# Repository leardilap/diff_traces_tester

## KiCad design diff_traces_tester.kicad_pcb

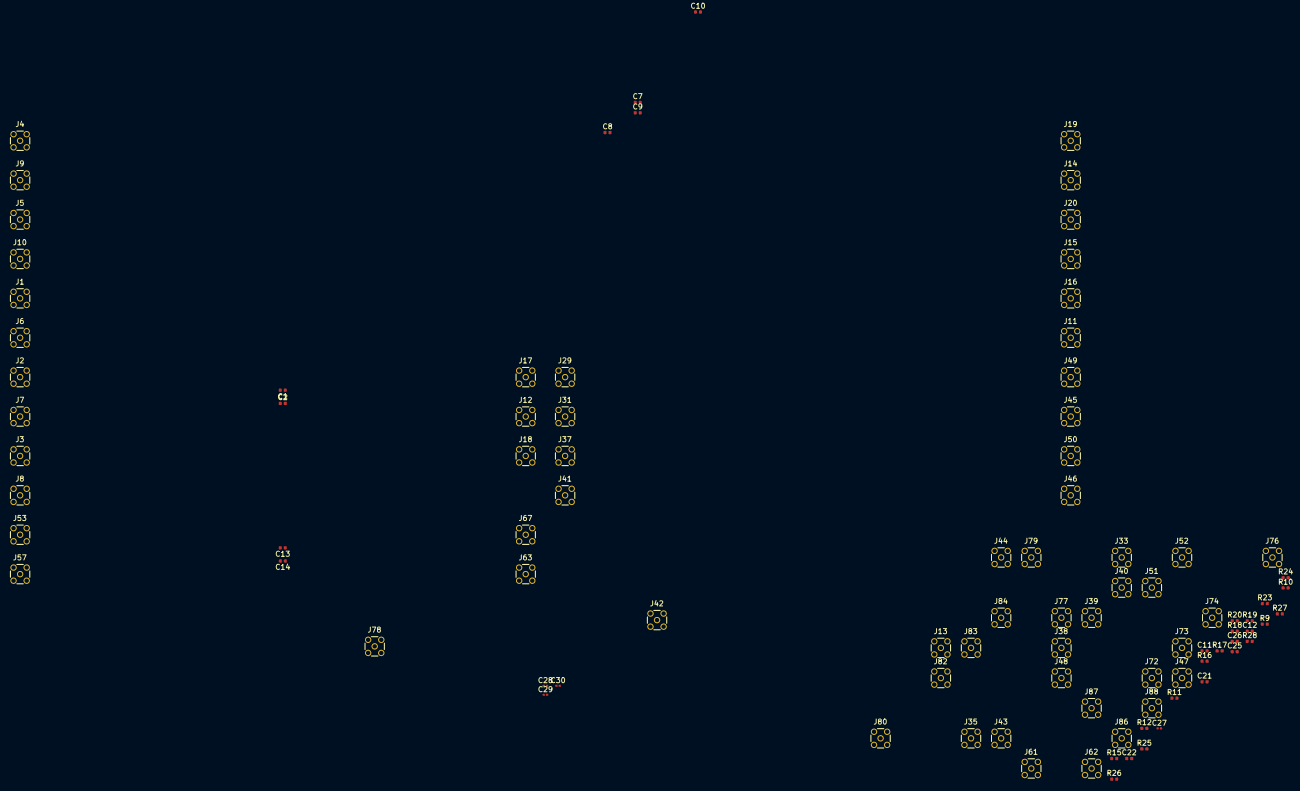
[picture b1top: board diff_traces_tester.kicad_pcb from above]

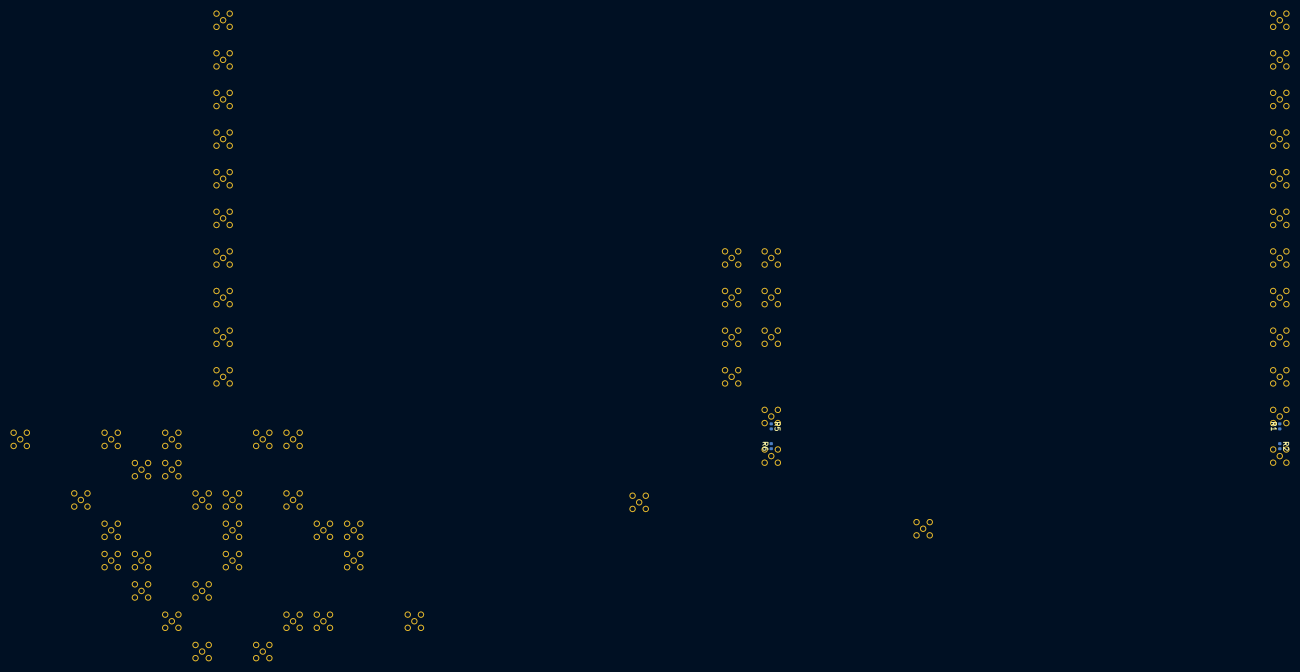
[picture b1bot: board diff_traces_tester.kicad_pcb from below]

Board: 2 copper layers, 98 parts (4 on the bottom side), 69 nets, no tracks yet.

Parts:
C1, C2, C7, C8, C9, C10, C11, C12, C13, C14, C21, C22, C25, C26: 0.1uF; C_0402_1005Metric
C27, C28, C29, C30: 0.1uF; C_0201_0603Metric
J1, J2, J3, J4, J5, J6, J7, J8, J9, J10, J11, J12, J13, J14, J15, J16, J17, J18, J19, J20, J29, J31, J33, J35, J37, J38, J39, J40, J41, J42, J43, J44, J45, J46, J47, J48, J49, J50, J51, J52, J53, J57, J61, J62, J63, J67, J72, J73, J74, J76, J77, J78, J79, J80, J82, J83, J84, J86, J87, J88: Conn_Coaxial; MMCX_Molex_73415-1471_Vertical
R1, R2, R5, R6, R9, R10, R11, R12, R15, R16, R17, R18, R19, R20, R23, R24, R25, R26, R27, R28: 0; R_0402_1005Metric

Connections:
/1_A_N: C14.2, R2.1
/1_A_P: C13.2, R1.1
/1_B_N: C14.1, R6.2
/1_B_P: C13.1, R5.2
/4_A_N: C26.2, R16.1
/4_A_P: C25.2, R15.1
/4_B_N: C26.1, R24.2
/4_B_P: C25.1, R23.2
/5_A_N: C22.2, R10.1
/5_A_P: C21.2, R9.1
/5_B_N: C22.1, R12.2
/5_B_P: C21.1, R11.2
/7_A_N: C28.2, R18.1
/7_A_P: C27.2, R17.1
/7_B_N: C28.1, R26.2
/7_B_P: C27.1, R25.2
/8_A_N: C30.2, R20.1
/8_A_P: C29.2, R19.1
/8_B_N: C30.1, R28.2
/8_B_P: C29.1, R27.2
/MS_45_2Stitch_N: J31.1, J33.1
/MS_45_2Stitch_P: J29.1, J35.1
/MS_45_4Stich_Cap_A_N: C8.2, J42.1
/MS_45_4Stich_Cap_A_P: C7.2, J38.1
/MS_45_4Stich_Cap_B_N: C8.1, J46.1
/MS_45_4Stich_Cap_B_P: C7.1, J50.1
/MS_45_4Stitch_N: J41.1, J45.1
/MS_45_4Stitch_P: J37.1, J49.1
/MS_45_N: J6.1, J11.1
/MS_45_NoVia_Cap_A_N: C2.2, J7.1
/MS_45_NoVia_Cap_A_P: C1.2, J2.1
/MS_45_NoVia_Cap_B_N: C2.1, J12.1
/MS_45_NoVia_Cap_B_P: C1.1, J17.1
/MS_45_P: J1.1, J16.1
/MS_ZigZag_4Stich_Cap_A_N: C12.2, J44.1
/MS_ZigZag_4Stich_Cap_A_P: C11.2, J40.1
/MS_ZigZag_4Stich_Cap_B_N: C12.1, J48.1
/MS_ZigZag_4Stich_Cap_B_P: C11.1, J52.1
/MS_ZigZag_N: J9.1, J14.1
/MS_ZigZag_P: J4.1, J19.1
/MS_round_4Stich_Cap_A_N: C10.2, J43.1
/MS_round_4Stich_Cap_A_P: C9.2, J39.1
/MS_round_4Stich_Cap_B_N: C10.1, J47.1
/MS_round_4Stich_Cap_B_P: C9.1, J51.1
/MS_round_N: J8.1, J13.1
/MS_round_P: J3.1, J18.1
/MS_straight_N: J10.1, J15.1
/MS_straight_P: J5.1, J20.1
GND: J1.2, J2.2, J3.2, J4.2, J5.2, J6.2, J7.2, J8.2, J9.2, J10.2, J11.2, J12.2, J13.2, J14.2, J15.2, J16.2, J17.2, J18.2, J19.2, J20.2, J29.2, J31.2, J33.2, J35.2, J37.2, J38.2, J39.2, J40.2, J41.2, J42.2, J43.2, J44.2, J45.2, J46.2, J47.2, J48.2, J49.2, J50.2, J51.2, J52.2, J53.2, J57.2, J61.2, J62.2, J63.2, J67.2, J72.2, J73.2, J74.2, J76.2, J77.2, J78.2, J79.2, J80.2, J82.2, J83.2, J84.2, J86.2, J87.2, J88.2
unnamed: J53.1, R1.2
unnamed: J57.1, R2.2
unnamed: J61.1, R9.2
unnamed: J62.1, R10.2
unnamed: J63.1, R6.1
unnamed: J67.1, R5.1
unnamed: J72.1, R15.2
unnamed: J73.1, R17.2
unnamed: J74.1, R19.2
unnamed: J76.1, R16.2
unnamed: J77.1, R18.2
unnamed: J78.1, R20.2
unnamed: J79.1, R12.1
unnamed: J80.1, R11.1
unnamed: J82.1, R24.1
unnamed: J83.1, R26.1
unnamed: J84.1, R28.1
unnamed: J86.1, R23.1
unnamed: J87.1, R25.1
unnamed: J88.1, R27.1
